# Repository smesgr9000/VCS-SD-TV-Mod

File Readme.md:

# VCS-SD-TV-Mod

VCD-SD-TV-Mod are two addon board for your **Atari VCS/2600 Jr** (Junior) game consoles. It will allow the user to **switch** between the analog **television signal** and standard definition (SD) video using a **composite video** connector. Most Mods normally remove the TV functionallity from the console.

Currently the mod is only tested on **CO21503 REV B, F** and **F1** devices! Other may likely **not** work!

- [boards](#boards)
   - [vcsboard](#vcsboard)
   - [outputboard](#outputboard)
- [ordering boards](#ordering-boards)
- [build boards](#build-boards)
   - [coil configuration](#coil-configuration)
   - [cable pinout](#cable-pinout)
- [install boards](#install-boards)
   - [for A and B](#for-a-and-b)
   - [only A](#only-a)
   - [only B](#only-b)
- [setup the board](#setup-the-board)
- [license](#license)

## boards

The mod uses two boards. _vcsboard_ for the logic chip and TV functionallity. _outputboard_ for the actual switch and composite output. It is possible to use only the _outputboard_ if TV signals aren't needed.

### vcsboard

The board plays "man in the middle" and uses audio (J3), video (J2), VCC (J1) and GND (J5) from the Junior and redirect it through a switch. Then the multiplexer either forward those signals to the _outputboard_ or parts of the TV generation circuit replaced by the board itself. First iteration used the original components of the junior. But to fit the circuit under the electromagnetic shield and keep the PCB production price low most of the components are replaced by more modern smaller surface mounted parts.

_Some revision. Latest on the left_

### outputboard

The board contains the actual switch and a LED to show the current selected output type as well as the composite modulation and a 3.5mm TRS jack for outputing the signal. The pinout of the Jack is:

Part | Description
--- | ---
Tip | Video
Ring 1 | Left Audio
Ring 2 | Right Audio*
Sleeve | Groud

Be aware there are several standards cables out there. Most have ground on the sleeve thus went with this design. The RCA jacks may be connected with the "wrong" colors but will work. If your cable has ground on first or second ring the MOD will not work, have alot of noise on the display or worst destroy something (unlikly but be rather safe than sorry and test your cable before hand!)

Because the Atari VCS/2600 is mono only just the first ring has an audio signal. If you want to drive both channels with the same signal bridge the _JP1_ on the _outputboard_.

_Some revision. Latest on the left_

## ordering boards

To order the latest version. Open _outputboard_ or _vcsboard_ in KiCad with the KiCad PCB-Editor. Use _Fabrication Output_ > _Gerber_ and select an output folder and agree with _Plot_ with the default configruation. Also use _Fabrication Output_ > _Drill Files_ than select the same output folder and agree with _Generate Drill File_. 

The ordering and manufacturing depends on your selected PCB manufacturer. For www.pcbway.com:

- enter length/width (33mm x 31.5mm for _vcsboard_; 33.9mm x 23.5mm _outputboard_)
- 2 layers
- 0.8mm thickness
- FR4
- TG 150-160
- 6/6mil Min Tracking
- 0.3mm Hole Size
- Solder Mask - any is fine
- Silkscreen - any is fine
- No Edge Connector
- Finish - any is fine but would suggest HASL
- Tending Vias
- 1oz Finish Copper

Upload a zip containing the above generated files. Currently the price for 5 boards should be 5$ for both designs.

## build boards

there are two possibilities.

- **A** only the outputboard without TV functionallity and only composite
- **B** both boards with TV functionallity and composite

For both variants soldering is required. 

Part | For
--- | ---
C33, R17, R56, Q4 | A, B
C49, C53, C54, L8, R43, R48 | B
L6 | A (optional)
C52 | B (optional)

If you want to reuse coil L8 on the _vcsboard_ please remove this part gently. The other parts are not reused. Also be aware sometimes a second coil is also attached to L8 on the underside of the board. If you want to reuse those you have to recreate the setup on the _vcsboard_. But I would suggestion replace this setup with new coils because it could be rather cramped below the shield.

L6 for **A** is optional and could be used to bring cables to the _outputboard_. Do **NOT** remove this for **B**! C52 for **B** is optional but make it easier to install the _vcsboard_ later.

![Image of CO21503 Rev F with components to remove. C54 is the most right bottom component of the complete board. Than to the left C53, R43, C52, R56. Above C54 is L8 than to the left R48, C49. Above L8 are three components not to remove followed by C33. And left of C33 is R17 also around half a centimeter above C33. L6 is further to the left, after a DIP16 chip and three axial or one radial mounted components.](<./CO21503 RevF Remove.jpg>)
_Image of components to remove for CO21503 REV F in blue for **A** and red for **B**_

Following parts are needed for the _outputboard_:

Reference | Part | Amount | For | Additional Information
--- | --- | --- | --- | ---
D1 | Kingbright KM23ESGW | 1 | A, B (optional) | only needed if you want a LED, recommended for **B**
J1 | Amtek 2542R-05TW-L | 1 | A, B (optional) | not needed if cables are soldered directly to the PCB. Other 2.54mm socket could be e.g. a JH2.54 with 5 pins
X | Amtek 2544H-05R-L | 1 | A, B (optional) | if above is used
J2 | Tensility 54-00177 | 1 | A, B |
Q1 | Nexperia PMBT2222A | 1 | A, B | or Yangzhou MMBT2222A
R1 | Yageo RC1206JR-072K2L | 1 | A, B |
R2 | Yageo RC1206JR-073K3L | 1 | A, B |
R3 | Yageo RC1206JR-0775RL | 1 | A, B |
R4 | Yageo RC1206FR-07120RL | 1 | B (optional) | only needed if you want a LED. Resistence could be increased if red light is to bright for your taste
R5 | Yageo RC1206FR-13150RL | 1 | A, B (optional) | only needed if you want a LED. Resistence could be increased if green light is to bright for your taste
SW1 | Würth WS-SLSU 450404015514 | 1 | B |

For **A** the SW1 left and middle pad must be bridged! The jack will have no video signal if this is skipped.

Following parts are needed for the _vcsboard_ (**B**):

Reference | Part | Amount |  Additional Information
--- | --- | --- | ---
C2, C49 | Yageo CC1206KRX7R9BB104 | 2 |
C33 | Yageo CC1206JRNPO9BN101 | 1 |
C52 | Yageo CC1206JRNPO9BN470 | 1 |
C53, C54 | Panasonic ECH-U1H821GX5 | 2 |
J1, J2, J3, J5 | MPE Garry 087-1-004 | 1 | or Amphenol G800LW304032EU - cut into 4 parts, more pins can be used for X2 and X4
J4 | Amtek 2542R-06TW-L | 1 | not needed if cables are soldered directly to the PCB. Other 2.54mm socket could be e.g. a JH2.54 with 6 pins
X | Amtek 2544H-06R-L | 1 | if above is used
L8 | Coilcraft 148-13J12L | 1 | not needed if original L8 is not reused. Other Coilcraft trimable coils are possible with L8a.
L8a1 | TDK TFM201210ALMA1R5MTAA | 1 | not needed if original L8 is used or another trimable coil which fits the original coil.
Q4 | Nexperia PMBT2222A | 1 |
R17 | Yageo RC1206JR-07330RL | 1 |
R43 | Yageo RC1206JR-079K1L | 1 |
R48 | Yageo RC1206JR-0718KL | 1 |
R56 | Yageo RC1206JR-071K8L | 1 |
U1 | Texas Instruments CD4053BM | 1 |

### coil configuration
Coil L8/L8a1 should be trimable around 2µH. If L8a1 is not used both pads must be bridged! If this step is skipped the circuit is open and will not work.
Be aware there are two possible combinations of holes. The pin 1 next to X4 should always be connected. Depending on the coil you could either use the pin labled 2
(for Coilcraft 148-series or the Atari coil) or the pin further in (for Coilcraft 148-series). The pin in between is for stability only and is not
connected to any other component.
All coils should be placed axial, otherwise it will not fit under the shield. The Coilcraft 143 is the easiest to install.

If you want to use Coilcraft 148 the top pin could be bent and the other pin connected via cable or via a pin header. You may want to use some glue to fix it down.

If you want to use the original Atari coil with metal housing use two or three pin headers. Additionally you may want to use both pads to fix it down.
Please check if you have a setup were two coils where installed in parallel (one was located on the bottom of the Atari board).

### cable pinout

The cable pinout for J4 on the _vcsboard_ with recommended cable color. Every pin is labeled on PCB:
- TV Selected aka Vtv (Orange)
- VCC (Red)
- Video (Yellow)
- Ground (Black)
- Audio (White)
- TV (Brown)

The cable pinout for J1 on the _outputboard_ with recommended cable color. Every pin is labeled on back of PCB:
- TV Selected aka Vtv (Orange) **not** needed for **A**
- VCC (Red)
- Video (Yellow)
- Ground (Black)
- Audio (White)

## install boards

### for A and B
The U-shaped _outputboard_ should fit perfectly around the tv jack (J4). I would suggest to use one to three sticky 40 by 40mm foam pads 
under the _outputboard_ to put into place. Drill one or two holes to the left and right into the back of the tv jack.
The second hole is only needed if you want a LED or require the switch (**B**).

The cable length between the boards should be 20-22cm depending on route and connector used. For the TV signal (brown cable)
18cm should work fine.

Otherwise it is possible to avoid drilling by squeezing cables out of the exisiting hole at underside of the system board.

### only A
Either use the existing hole in the shield to lead the cable out on the top side or if L6 was removed connect all cables 
from the bottom and bring it to the top from the hole at L6.

Connect the follwing parts with the _outputboard_:
- VCC with Q4 right pin
- Video with R56 top pin
- Ground with R43 top pin
- Audio with C49 bottom pin

### only B
Connect _outputboard_ J1 with _vcsboard_ J4 as described above. TV to the left pin hole of the removed R17 component.
Optionally you could also install a connector here. Cut pin header into 4 pieces and solder the shorter part into:
- J1 to Q4 right pin
- J2 to R56 top pin
- J3 to C49 bottom pin
- J5 to R43 top pin

You could also add a pin header to C54 bottom pin and C49 top pin for stability.

## setup the board

Install shield again and power up the device. SD mode should work without setup. The TV mode require some tuning.
If tv signal is off turn L6 until video sginal is good again. If audio is noisy turn L8 until noise goes away. If the
audio still noisy even if the core is fully in or out. Check if your coil setup is really around 2µH or you have
a different Atari coil which had afaik 2.5µH and more and required a second coil in parallel to bring it back down to 2µH.

_older revision installed of vcsboard with Coilcraft 148 setup and outputboard_

# license

Project uses [Attribution-ShareAlike 4.0 International](./LICENSE)

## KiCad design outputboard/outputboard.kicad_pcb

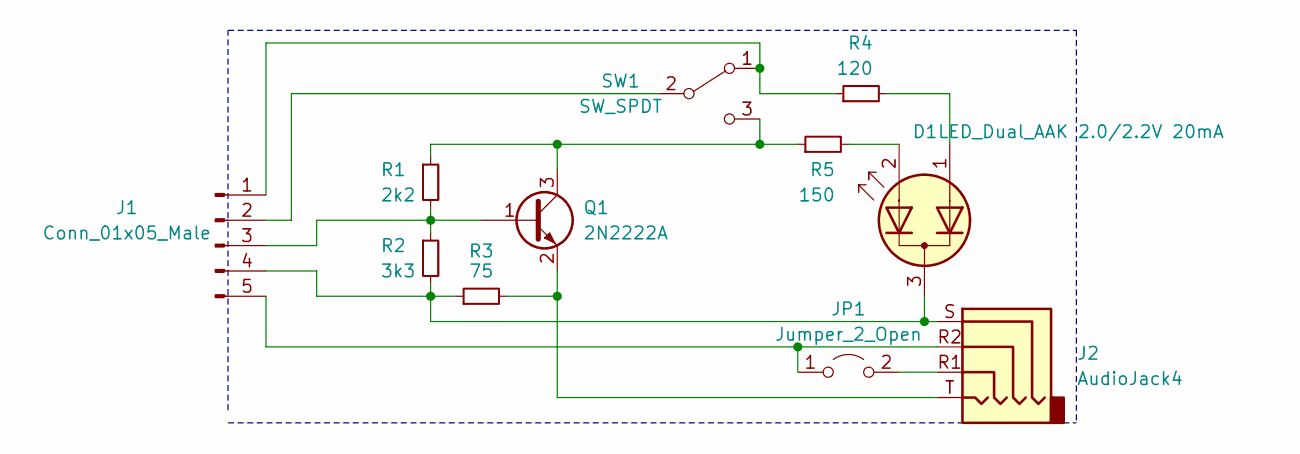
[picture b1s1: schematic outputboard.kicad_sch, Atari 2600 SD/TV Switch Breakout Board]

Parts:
D1: LED_Dual_AAK 2.0/2.2V 20mA; SOT-23_Handsoldering; Part Kingbright KM23ESGW
J1: Conn_01x05_Male; Molex_KK-254_AE-6410-05A_1x05_P2.54mm_Vertical; Part Amtek 2542R-05TW-L
J2: AudioJack4; 54-00177; Part Tensility 54-00177
JP1: Jumper_2_Open; Jumper_2_1.27_Open
Q1: 2N2222A; SOT-23_Handsoldering; Part Nexperia PMBT2222A
R1: 2k2; R_1206_3216Metric_Pad1.30x1.75mm_HandSolder; Part Yageo RC1206JR-072K2L
R2: 3k3; R_1206_3216Metric_Pad1.30x1.75mm_HandSolder; Part Yageo RC1206JR-073K3L
R3: 75; R_1206_3216Metric_Pad1.30x1.75mm_HandSolder; Part Yageo RC1206JR-0775RL
R4: 120; R_1206_3216Metric_Pad1.30x1.75mm_HandSolder; Part Yageo RC1206FR-07120RL
R5: 150; R_1206_3216Metric_Pad1.30x1.75mm_HandSolder; Part Yageo RC1206FR-13150RL
SW1: SW_SPDT; WS-SLSU; Part Würth WS-SLSU 450404015514

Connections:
unnamed: D1.1 (A2), R4.2
unnamed: D1.2 (A1), R5.2
unnamed: D1.3 (K), J1.4, J2.S, R2.2, R3.1
unnamed: J1.1, R4.1, SW1.1 (A)
unnamed: J1.2, SW1.2 (B)
unnamed: J1.3, Q1.1 (B), R1.2, R2.1
unnamed: J1.5, J2.R2, JP1.1 (A)
unnamed: J2.R1, JP1.2 (B)
unnamed: J2.T, Q1.2 (E), R3.2
unnamed: Q1.3 (C), R1.1, R5.1, SW1.3 (C)

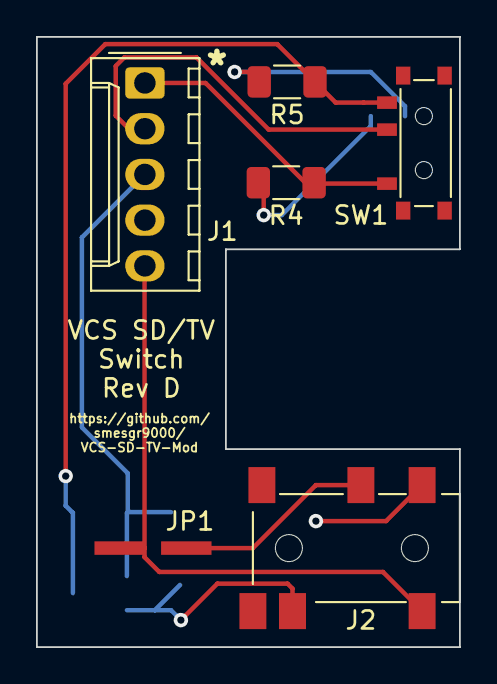
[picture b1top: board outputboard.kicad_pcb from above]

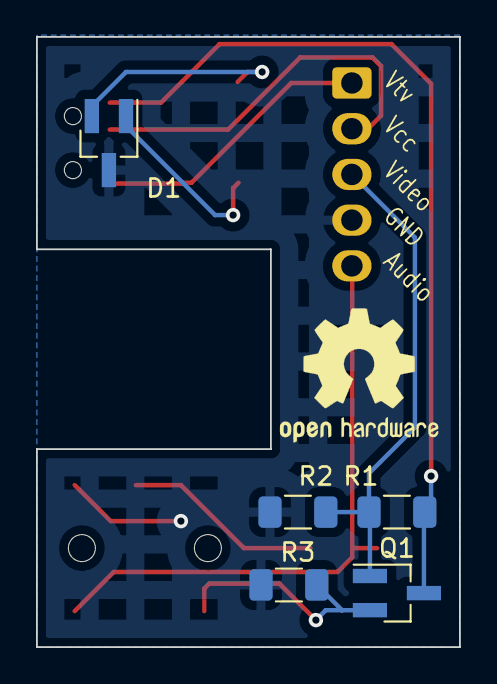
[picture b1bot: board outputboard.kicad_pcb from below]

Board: 2 copper layers, 23.5 x 33.9 mm, 11 parts (5 on the bottom side), 10 nets.

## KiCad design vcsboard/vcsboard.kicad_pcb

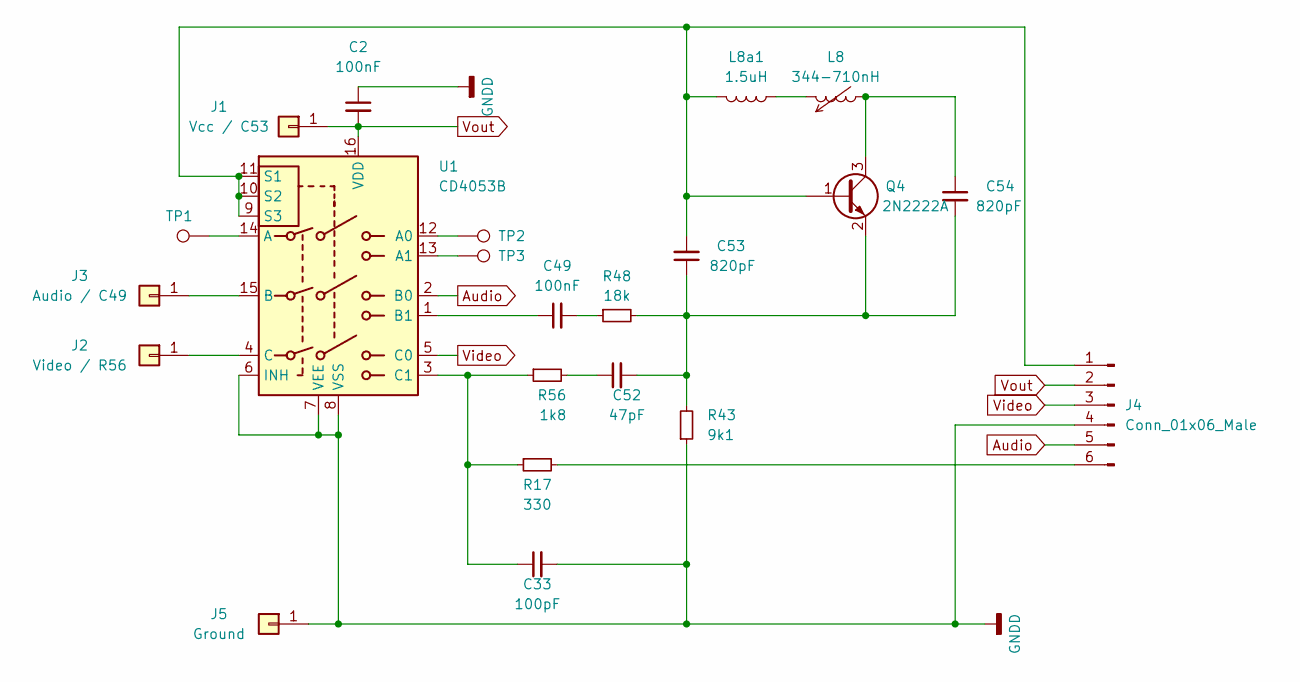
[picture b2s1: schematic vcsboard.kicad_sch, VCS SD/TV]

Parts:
C2, C49: 100nF; C_1206_3216Metric_Pad1.33x1.80mm_HandSolder; Part Yageo CC1206KRX7R9BB104
C33: 100pF; C_1206_3216Metric_Pad1.33x1.80mm_HandSolder; Part Yageo CC1206JRNPO9BN101
C52: 47pF; C_1206_3216Metric_Pad1.33x1.80mm_HandSolder; Part Yageo CC1206JRNPO9BN470
C53, C54: 820pF; C_0805_2012Metric_Pad1.18x1.45mm_HandSolder; Part Panasonic ECH-U1H821GX5
J1: Vcc / C53; SolderWire-0.75sqmm_1x01_D1.25mm_OD2.3mm
J2: Video / R56; SolderWire-0.75sqmm_1x01_D1.25mm_OD2.3mm; Part MPE Garry 087-1-004
J3: Audio / C49; SolderWire-0.75sqmm_1x01_D1.25mm_OD2.3mm
J4: Conn_01x06_Male; Molex_KK-254_AE-6410-06A_1x06_P2.54mm_Vertical; Part Amtek 2542R-06TW-L
J5: Ground; SolderWire-0.75sqmm_1x01_D1.25mm_OD2.3mm
L8: 344-710nH; tim_laying; Part Coilcraft 148-13J12L
L8a1: 1.5uH; L_0805_2012Metric_Pad1.05x1.20mm_HandSolder; Part TDK TFM201210ALMA1R5MTAA
Q4: 2N2222A; SOT-23_Handsoldering; Part Nexperia PMBT2222A
R17: 330; R_1206_3216Metric_Pad1.30x1.75mm_HandSolder; Part Yageo RC1206JR-07330RL
R43: 9k1; R_1206_3216Metric_Pad1.30x1.75mm_HandSolder; Part Yageo RC1206JR-079K1L
R48: 18k; R_1206_3216Metric_Pad1.30x1.75mm_HandSolder; Part Yageo RC1206JR-0718KL
R56: 1k8; R_1206_3216Metric_Pad1.30x1.75mm_HandSolder; Part Yageo RC1206JR-071K8L
TP1, TP2, TP3: TestPoint; TestPoint_THTPad_1.5x1.5mm_Drill0.7mm
U1: CD4053B; SOP-16_3.9x9.9mm_P1.27mm; Part Texas Instruments CD4053BM

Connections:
Audio: J4.5, U1.2 (B0)
GNDD: C2.1, C33.2, J4.4, J5.1, R43.1, U1.6 (INH), U1.7 (VEE), U1.8 (VSS)
unnamed: C33.1, R17.1, R56.1, U1.3 (C1)
unnamed: C49.1, U1.1 (B1)
unnamed: C49.2, R48.1
unnamed: C52.1, R56.2
unnamed: C52.2, C53.1, C54.2, Q4.2 (E), R43.2, R48.2
unnamed: C53.2, J4.1, L8a1.2, Q4.1 (B), U1.9 (S3), U1.10 (S2), U1.11 (S1)
unnamed: C54.1, L8.2, Q4.3 (C)
unnamed: J2.1, U1.4 (C)
unnamed: J3.1, U1.15 (B)
unnamed: J4.6, R17.2
unnamed: L8.1, L8a1.1
unnamed: TP1.1, U1.14 (A)
unnamed: TP2.1, U1.12 (A0)
unnamed: TP3.1, U1.13 (A1)
Video: J4.3, U1.5 (C0)
Vout: C2.2, J1.1, J4.2, U1.16 (VDD)

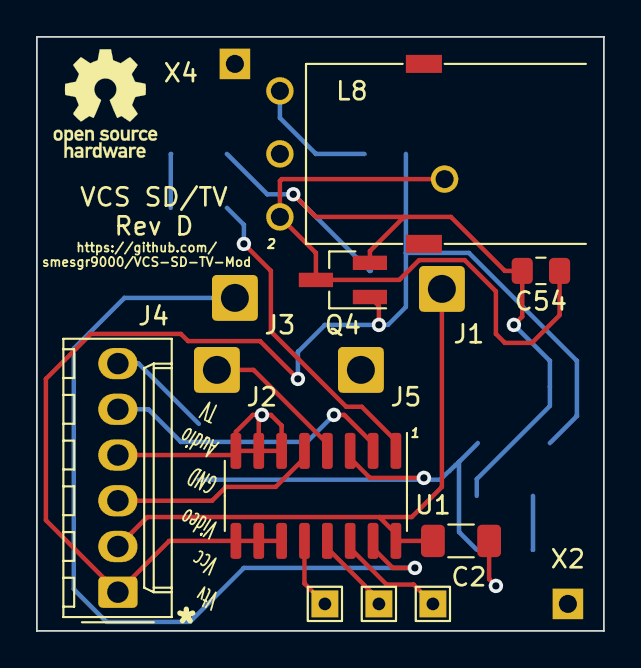
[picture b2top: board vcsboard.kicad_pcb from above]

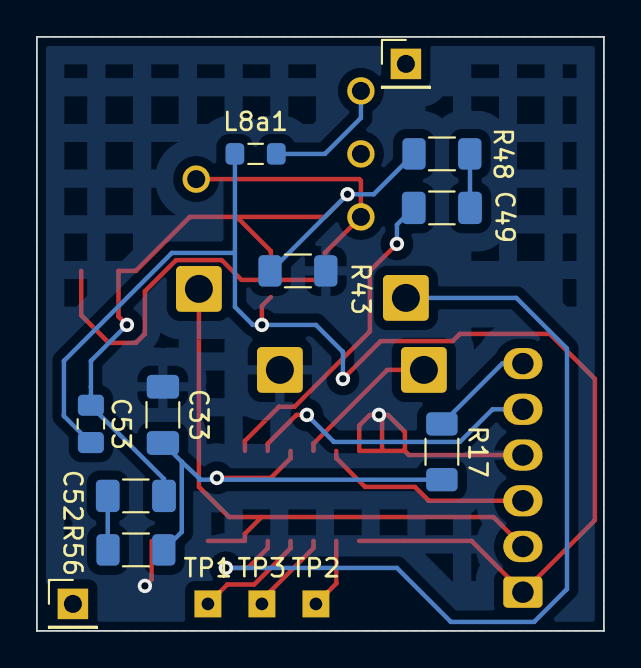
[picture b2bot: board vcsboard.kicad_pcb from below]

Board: 2 copper layers, 31.5 x 33.0 mm, 24 parts (11 on the bottom side), 18 nets.

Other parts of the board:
X2, X4: PinHeader_1x01_P2.54mm_Vertical

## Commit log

2023-01-26 fix warning of C1
2023-02-18 add part description for more complex parts, remove unused cap
2023-02-25 add some more parts, use 0805 components for C53 & C54
2023-02-25 add first draft of documentation, add another alternative
2023-02-25 fix docu
2023-02-25 typos
2023-02-25 add star to first pin
2023-03-05 add some more informations about cable management
2023-03-05 Update Readme.md
    fix typos in pictures links
2023-03-05 add a chapter how to order the boards
2023-09-03 add alternative for the 2N2222A
2024-12-20 update to Kicad 8
